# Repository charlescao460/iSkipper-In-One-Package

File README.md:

iSkipper-In-One-Package
=======================
An integration of Arduino and RFM69HW for an audience response system.

Versions
----
For the hardwares, there are currently two available versions: ***Ver.1.0.2*** and ***Ver.2.0.2***. (The Ver.1.0.0-1.0.1, Ver.2.0.0-2.0.1 are not perfectly useable).

The softwares should be compatible with all versions of hardwares.

### Ver.2.0.2

**Size:** 50mm x 26mm (including USB connector), 35mm x 26mm (without USB connector)

**MCU:** ATmega328P-MU (QFN-32)

**USB to Serial:** CH340E (MSOP-10)

**RF:** RFM69HW

**Level-shifting:** TXB0106RGYR (VQFN-16)

**3.3V power supply:** LP5907MFX-3.3 (SOT23-5)

**Antenna:** patch antenna (theoretically 3dbi gain)

**Resistors/Capacitors:** 0603

The Ver.2.X.X version is designed to minimize board's size, maximize portability and invisibility. Thus, the possibly smallest packages are selected. For example, the patch antenna, QFN-packaged chips, 0603 Resistors/Capacitors are used. Although it still practicable to solder it manually, it would be hard to do so without solder paste. Besides, you would need to burn Arduino's bootloader into ATmega328P-MU before soldering. Burning bootloader would require a QFN-32 dock, or other additional cost.

There are four holes on the board reserved for case installing. If you are going to use screws to install Acrylic case, please notice that the metal screws near the patch antenna would influence antenna's performances.

### Ver.1.0.2

**Size:** 90mm x 26mm (with connectors), 68mm x 26mm (without connectors)

**MCU:** ATmega328P-AU (QFP-32)

**USB to Serial:** CH340G (SOP-16)

**RF:** RFM69HW

**Level-shifting:** None (but it still work)

**3.3V power supply:** LM1117-3.3 (SOT223) (AMS1117 is also selectable)

**Antenna:** external antenna (with SMA connector)

**Resistors/Capacitors:** 1206

The Ver.1.X.X version is the first design of this project. It is basically a combination of Arduino Nano and RFM69HW. The original goal of this design is make it to be easy-manufactured. Thus, all components are big enough to solder with the normal soldering equipments and materials.

Some useful pin headers are reserved for burning bootloader or debugging. 

This version requires external antenna for better RF performance. The high-gain antennas would improve receiving performances. However, the overall size of this board would then be very big. (And if you are using this in public, the flaring LEDs and long antenna would catch everyone's eyes:) 

Notes
------
ATmega328P is working on 5 voltage, but RFM69HW requires 3.3 voltage. However, shockingly, they are stable and durable in daily use.

Update 2018/07/06: In Ver.2.0.0 design, I added a TXB0106 for level-shifting. So the logic level won't be a problem anymore. But I am still wondering why RFM69HW could work proper under 5.0V. To save money, you could still consider remove TXB0106 in your own disign. 

See also
--------
[iSkipper](https://github.com/wizard97/iSkipper) Original repository that inspired this project.

[iSkipper-Software](https://github.com/charlescao460/iSkipper-Software) 
The softwares (contains Arduino Sketch) designed for these boards.

Disclaimer
----------
**This project is only a special version of Arduino Nano.**

**THIS PROJECT IS NOT DESIGNED TO REPLACE, EMULATE, OR BE COMPATIBLE WITH ANY SPECIFIC PRODUCT OF ANY COMPANY.**

**ALL THE PICTURES AND DOCUMENTS OF THIS PROJECT DO NOT IMPLY ANY SPECIFIC USE OF THIS PROJECT.**

**CONTRIBUTORS OF THIS PROJECT ARE FREE OF RESPONSIBILITY OF ANY IMPROPER USE OF THIS PROJECT.**

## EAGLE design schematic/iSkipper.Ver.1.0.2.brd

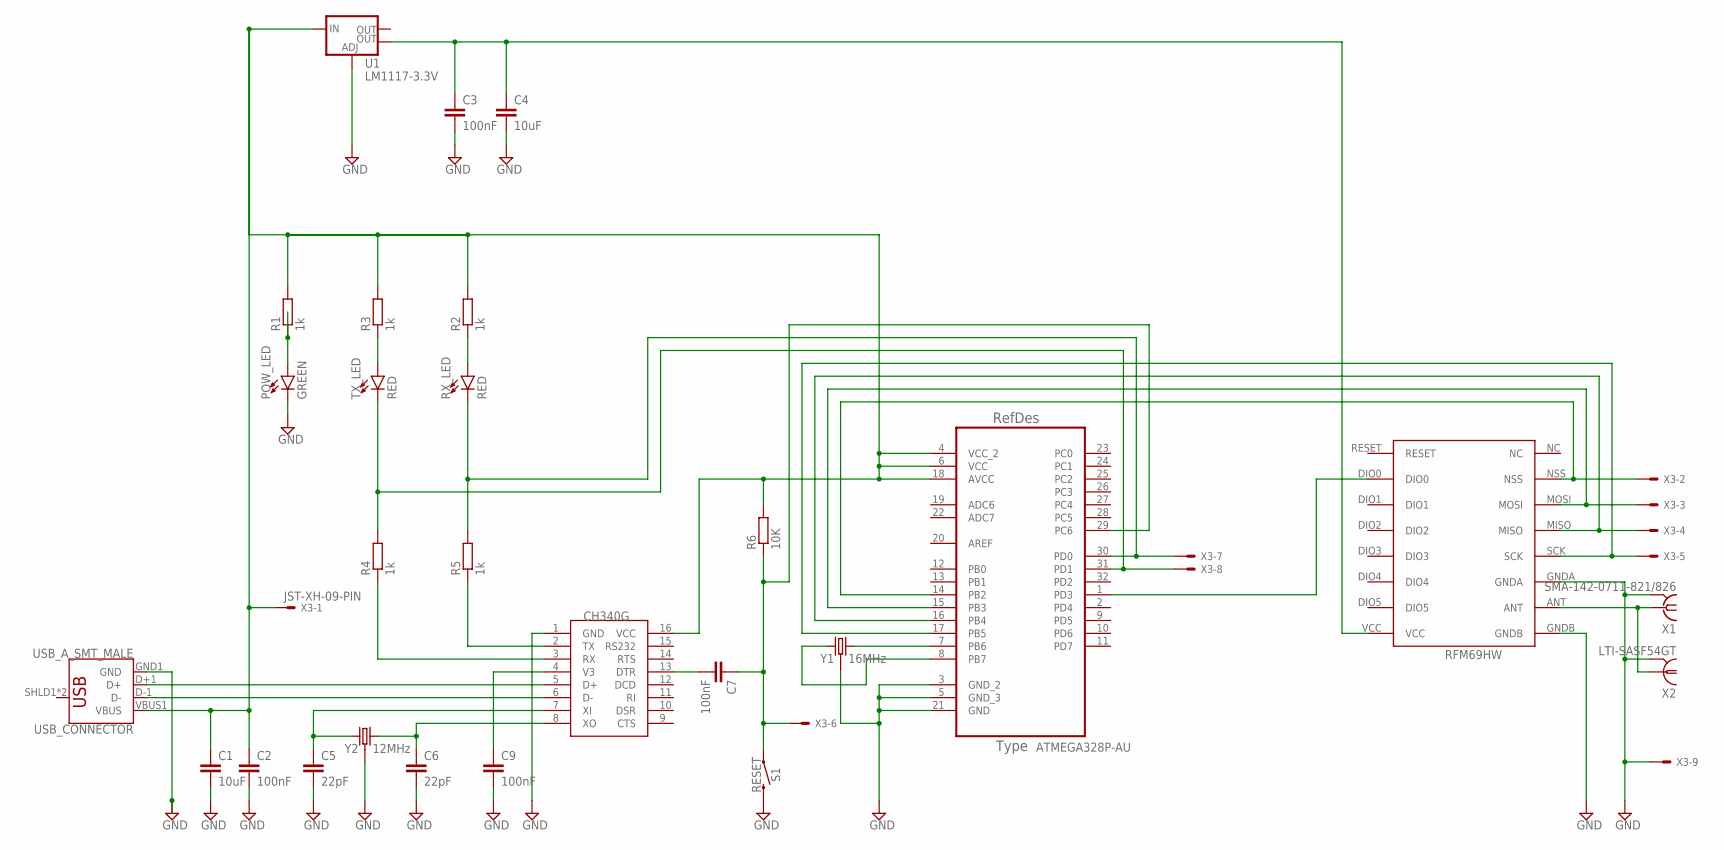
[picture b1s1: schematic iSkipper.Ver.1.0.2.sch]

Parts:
ATMEGA328P: ATMEGA328P-AU; QFP80P900X900X120-32N
C1, C4: 10uF; C1206
C2, C3, C7, C9: 100nF; C1206
C5, C6: 22pF; C1206
POW_LED: GREEN; LED-1206
R1, R2, R3, R4, R5: 1k; R1206
R6: 10K; R1206
RFM69HW: RFM69HW; RFM
RX_LED: RED; LED-1206
S1: RESET; TACTILE_SWITCH_SMD_5.2MM
TX_LED: RED; LED-1206
U1: LM1117-3.3V; SOT223
U$1: CH340G; SOIC16
USB_CONNECTOR: USB_A_SMT_MALE; USB-A-SMT-MALE
X1: SMA-142-0711-821/826; J502-ND-142-0711-821/826
X2: LTI-SASF54GT
X3: JST-XH-09-PIN; JST-XH-09-PACKAGE-ROUND-PAD-NO-SILK
Y1: 16MHz; CRYSTAL-SMD-3.2X2.5MM
Y2: 12MHz; CRYSTAL-SMD-3.2X2.5MM

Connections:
GND: ATMEGA328P.3 (GND_2), ATMEGA328P.5 (GND_3), ATMEGA328P.21 (GND), C1.2, C2.2, C3.2, C4.2, C5.2, C6.2, C9.2, POW_LED.C, RFM69HW.GNDA, RFM69HW.GNDB, S1.3 (2), U1.1 (ADJ), U$1.1 (GND), USB_CONNECTOR.GND1 (GND), X1.G@1 (2), X1.G@2 (2), X1.G@3 (2), X1.G@4 (2), X2.2, X2.3 (2), X2.4 (2), X2.5 (2), X3.9, Y1.2 (3), Y1.4 (3), Y2.2 (3), Y2.4 (3)
unnamed: ATMEGA328P.7 (PB6), Y1.3 (2)
unnamed: ATMEGA328P.8 (PB7), Y1.1
unnamed: ATMEGA328P.4 (VCC_2), ATMEGA328P.6 (VCC), ATMEGA328P.18 (AVCC), C1.1, C2.1, R1.2, R2.2, R3.2, R6.2, U1.3 (IN), U$1.16 (VCC), USB_CONNECTOR.VBUS1 (VBUS), X3.1
unnamed: U$1.5 (D+), USB_CONNECTOR.D+1 (D+)
unnamed: C3.1, C4.1, RFM69HW.VCC, U1.4 (OUT)
unnamed: POW_LED.A, R1.1
unnamed: R3.1, TX_LED.A
unnamed: U$1.6 (D-), USB_CONNECTOR.D-1 (D-)
unnamed: R2.1, RX_LED.A
unnamed: R5.1, U$1.2 (TX)
unnamed: C6.1, U$1.8 (XO), Y2.3 (2)
unnamed: C5.1, U$1.7 (XI), Y2.1
unnamed: R4.1, U$1.3 (RX)
unnamed: ATMEGA328P.31 (PD1), R4.2, TX_LED.C, X3.8
unnamed: ATMEGA328P.30 (PD0), R5.2, RX_LED.C, X3.7
unnamed: C7.2, U$1.13 (DTR)
unnamed: ATMEGA328P.29 (PC6), C7.1, R6.1, S1.1, X3.6
unnamed: RFM69HW.ANT, X1.1, X2.1
unnamed: C9.1, U$1.4 (V3)
unnamed: ATMEGA328P.17 (PB5), RFM69HW.SCK, X3.5
unnamed: ATMEGA328P.1 (PD3), RFM69HW.DIO0
unnamed: ATMEGA328P.14 (PB2), RFM69HW.NSS, X3.2
unnamed: ATMEGA328P.16 (PB4), RFM69HW.MISO, X3.4
unnamed: ATMEGA328P.15 (PB3), RFM69HW.MOSI, X3.3

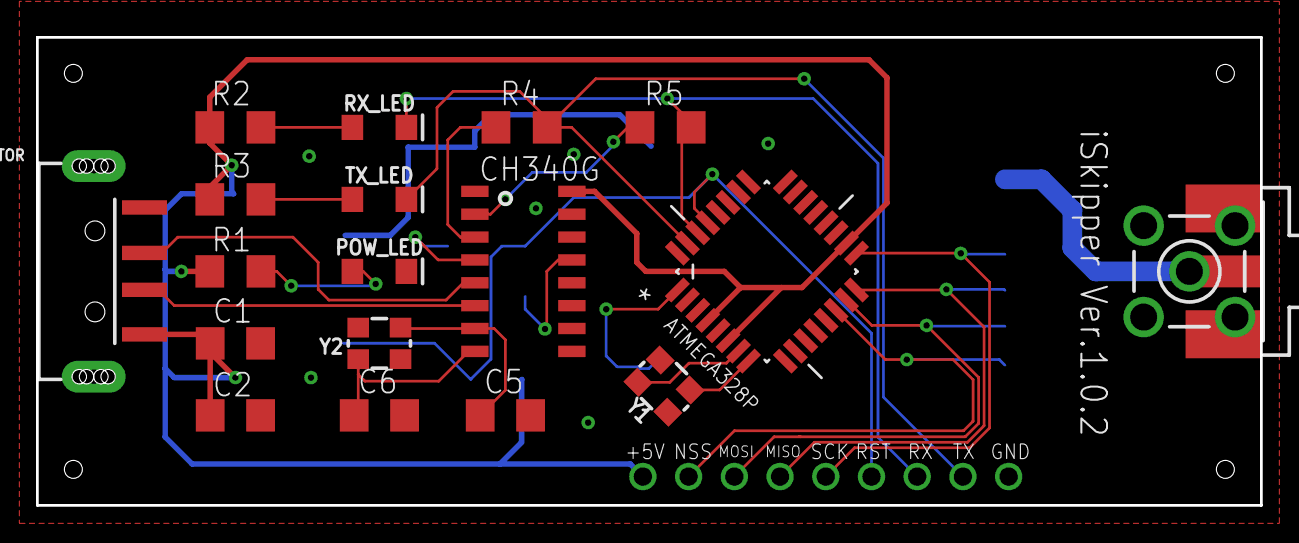
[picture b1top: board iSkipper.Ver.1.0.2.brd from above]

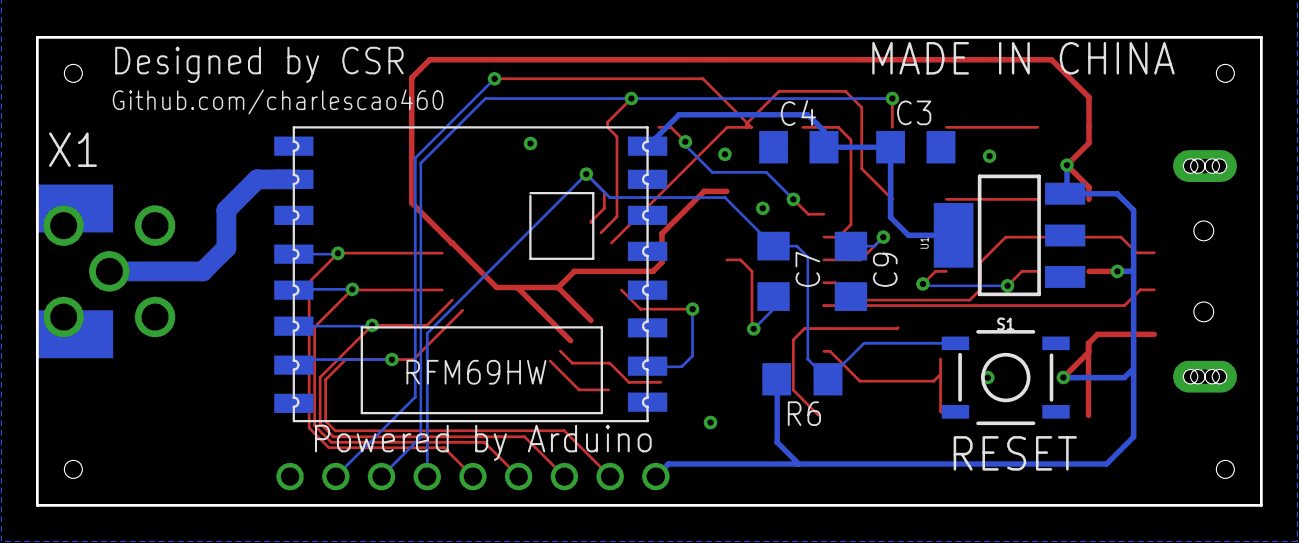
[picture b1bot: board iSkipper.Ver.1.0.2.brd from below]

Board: 2 copper layers, 68.0 x 26.0 mm, 28 parts (8 on the bottom side), 25 nets.

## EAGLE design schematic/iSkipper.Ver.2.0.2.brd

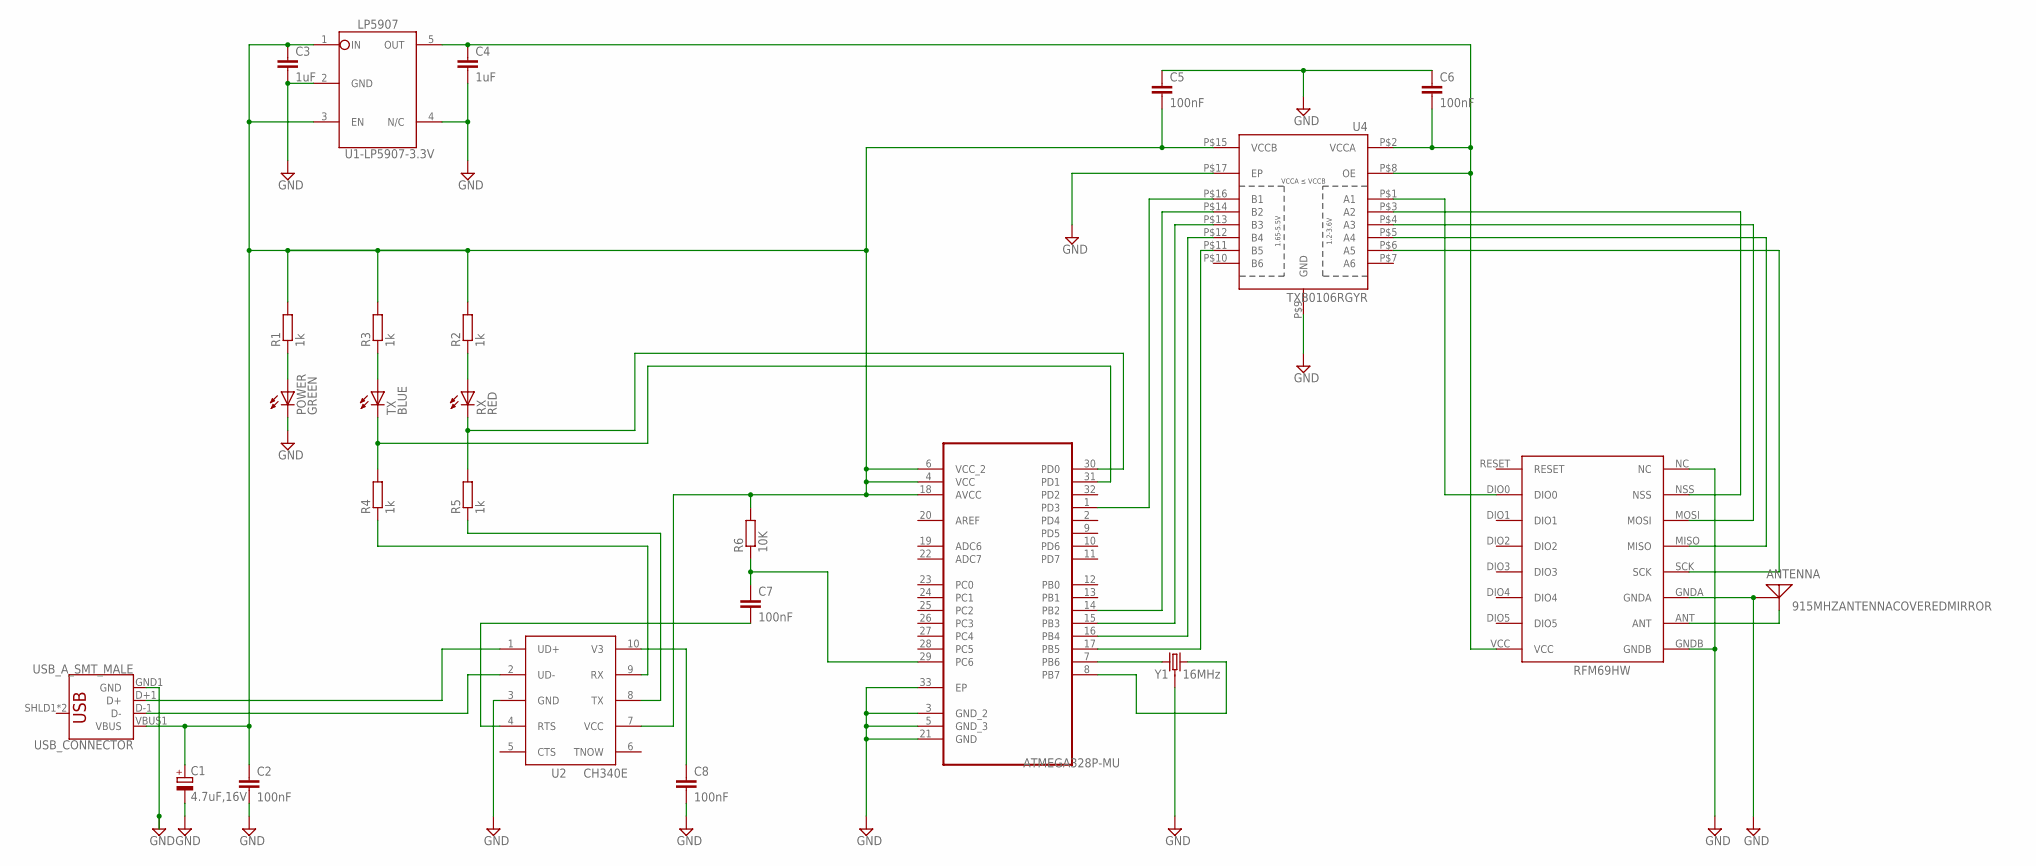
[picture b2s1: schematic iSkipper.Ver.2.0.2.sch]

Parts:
ANTENNA: 915MHZANTENNACOVEREDMIRROR; COVERED-MIRROR
C1: 4.7uF,16V; CT3216
C2, C5, C6, C7, C8: 100nF; C0603
C3, C4: 1uF; C0603
POWER: GREEN; SML0805
R1, R2, R3, R4, R5: 1k; R0603
R6: 10K; R0603
RFM69HW: RFM69HW; RFM
RX: RED; SML0805
TX: BLUE; SML0805
U2: CH340ESMD; MSOP10
U4: TXB0106RGYR; VQFN-16
U$1: U1-LP5907-3.3V; SOT-23
U$3: ATMEGA328P-MU; QFN50P500X500X100-33N
USB_CONNECTOR: USB_A_SMT_MALE; USB-A-SMT-MALE
Y1: 16MHz; CRYSTAL-SMD-3.2X2.5MM

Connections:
GND: ANTENNA.P$2 (GND), C1.-, C2.2, C3.2, C4.2, C5.1, C6.1, C8.2, POWER.C, RFM69HW.GNDA, RFM69HW.GNDB, RFM69HW.NC, U2.3 (GND), U4.P$9 (GND), U4.P$17 (EP), U$1.2 (GND), U$1.4 (N/C), U$3.3 (GND_2), U$3.5 (GND_3), U$3.21 (GND), U$3.33 (EP), USB_CONNECTOR.GND1 (GND), Y1.2 (3), Y1.4 (3)
unnamed: U$3.7 (PB6), Y1.1
unnamed: U$3.8 (PB7), Y1.3 (2)
unnamed: C1.+, C2.1, C3.1, C5.2, R1.2, R2.2, R3.2, R6.2, U2.7 (VCC), U4.P$15 (VCCB), U$1.1 (IN), U$1.3 (EN), U$3.4 (VCC), U$3.6 (VCC_2), U$3.18 (AVCC), USB_CONNECTOR.VBUS1 (VBUS)
unnamed: C7.2, U2.4 (RTS)
unnamed: U2.1 (UD+), USB_CONNECTOR.D+1 (D+)
unnamed: C4.1, C6.2, RFM69HW.VCC, U4.P$2 (VCCA), U4.P$8 (OE), U$1.5 (OUT)
unnamed: POWER.A, R1.1
unnamed: R3.1, TX.A
unnamed: U2.2 (UD-), USB_CONNECTOR.D-1 (D-)
unnamed: R2.1, RX.A
unnamed: R5.1, U2.8 (TX)
unnamed: C8.1, U2.10 (V3)
unnamed: R4.1, U2.9 (RX)
unnamed: U4.P$14 (B2), U$3.14 (PB2)
unnamed: R4.2, TX.C, U$3.31 (PD1)
unnamed: R5.2, RX.C, U$3.30 (PD0)
unnamed: U4.P$16 (B1), U$3.1 (PD3)
unnamed: C7.1, R6.1, U$3.29 (PC6)
unnamed: ANTENNA.P$1 (SIGNAL), RFM69HW.ANT
unnamed: RFM69HW.SCK, U4.P$6 (A5)
unnamed: RFM69HW.DIO0, U4.P$1 (A1)
unnamed: RFM69HW.NSS, U4.P$3 (A2)
unnamed: RFM69HW.MISO, U4.P$5 (A4)
unnamed: RFM69HW.MOSI, U4.P$4 (A3)
unnamed: U4.P$11 (B5), U$3.17 (PB5)
unnamed: U4.P$12 (B4), U$3.16 (PB4)
unnamed: U4.P$13 (B3), U$3.15 (PB3)

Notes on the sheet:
CH340E

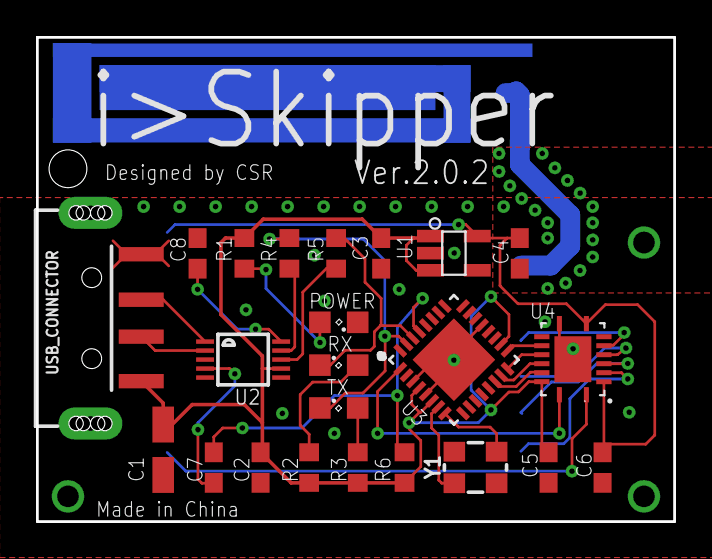
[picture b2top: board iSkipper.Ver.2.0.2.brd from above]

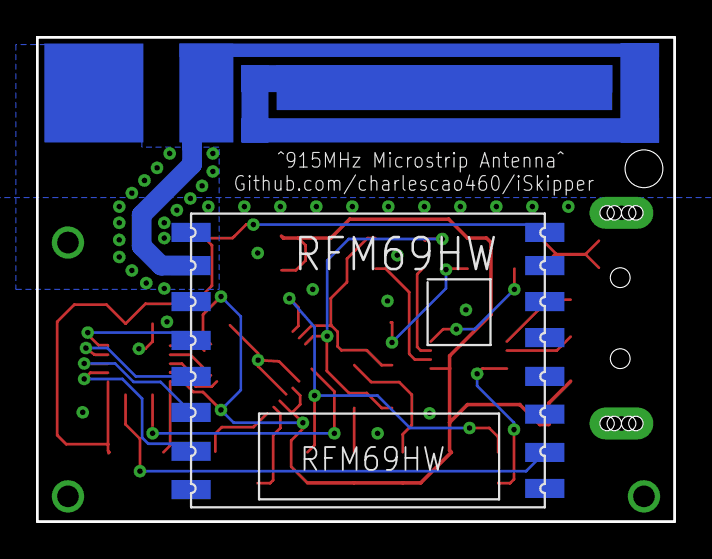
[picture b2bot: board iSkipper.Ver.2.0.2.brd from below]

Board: 2 copper layers, 35.4 x 26.9 mm, 25 parts (2 on the bottom side), 28 nets.

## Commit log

2018-08-09 Create Repository
2018-08-09 Create LICENSE
2018-08-09 Add .gitignore
2018-08-17 Update PCB files
2018-08-17 Remove corrupted designs
2018-08-26 Add Ver.2.0.2 pic
2018-08-27 Some Refactor
2018-08-27 Separate hardwares and software
2018-08-27 The software files were moved to new repos.
    https://github.com/charlescao460/iSkipper-Software

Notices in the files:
parts and their libraries:
SparkFun-Clocks: Licensing: Creative Commons ShareAlike 4.0 International - https://creativecommons.org/licenses/by-sa/4.0
